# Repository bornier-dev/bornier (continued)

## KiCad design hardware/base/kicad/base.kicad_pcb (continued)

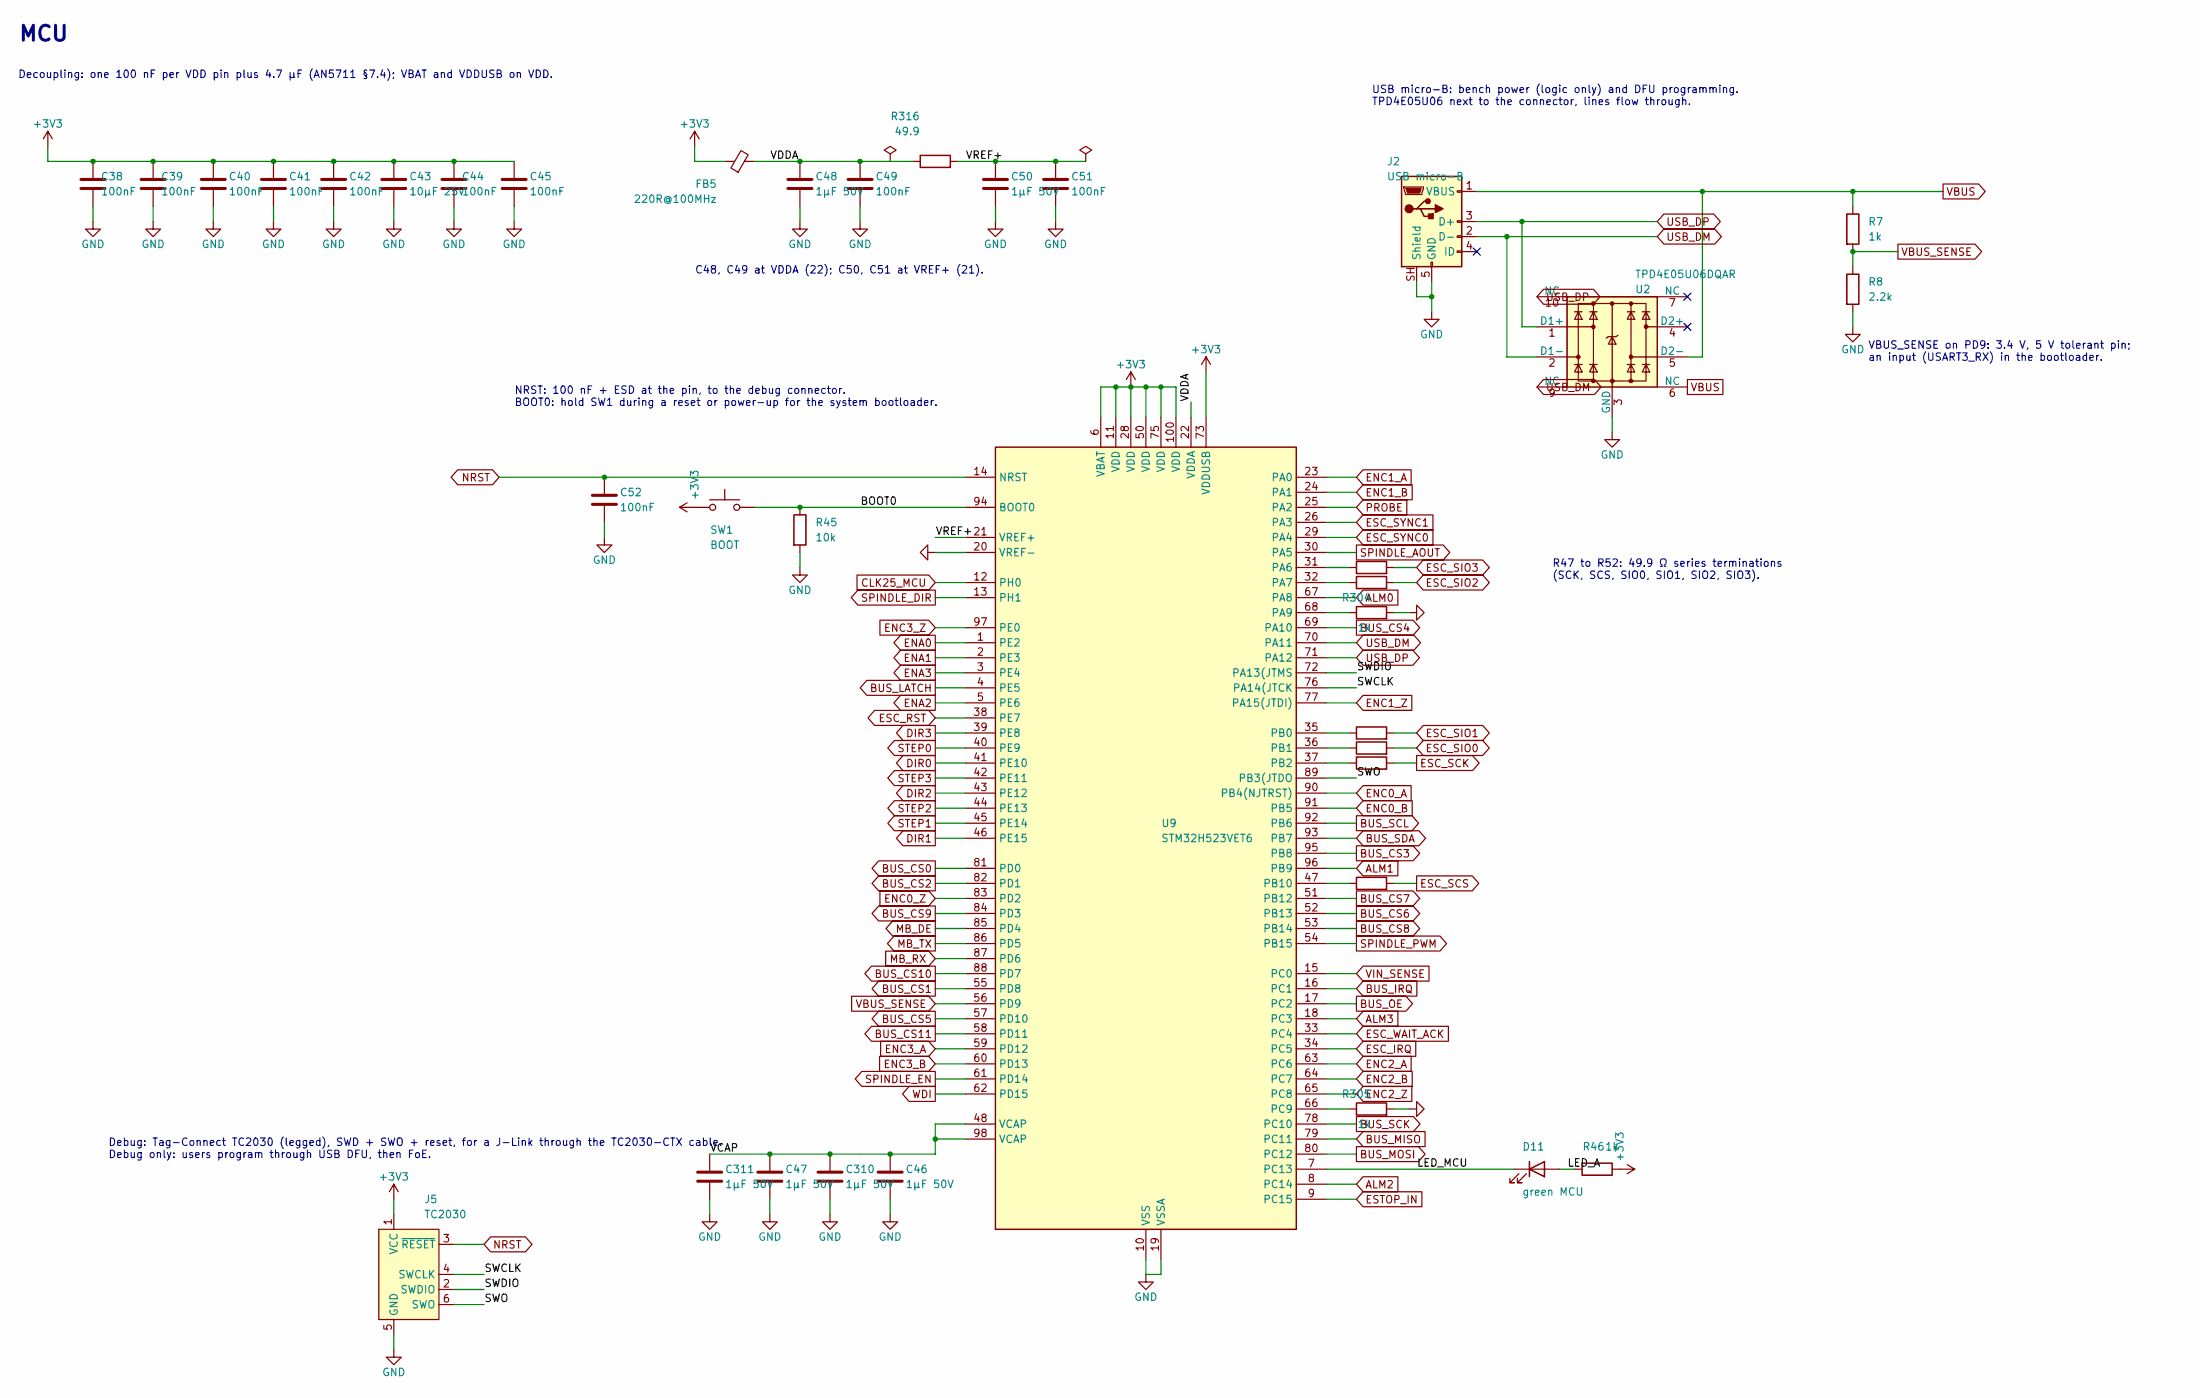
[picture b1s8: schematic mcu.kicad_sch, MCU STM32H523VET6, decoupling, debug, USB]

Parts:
C38, C39, C40, C41, C42, C44, C45, C49, C51, C52: 100nF; C_0402_1005Metric; LCSC C307331
C43: 10µF 25V; C_0805_2012Metric; LCSC C15850
C46, C47, C48, C50, C310, C311: 1µF 50V; C_0603_1608Metric; LCSC C15849
D11: green MCU; LED_0603_1608Metric; LCSC C2289
FB5: 220R@100MHz; L_0603_1608Metric; LCSC C80165
J2: USB micro-B; USB_Micro-B_Molex-105133-0001; LCSC C782257
J5: TC2030; Tag-Connect_TC2030-IDC-FP_2x03_P1.27mm_Vertical
R7, R46, R304, R305: 1k; R_0402_1005Metric; LCSC C11702
R8: 2.2k; R_0402_1005Metric; LCSC C25879
R45: 10k; R_0402_1005Metric; LCSC C25744
R47, R48, R49, R50, R51, R52, R316: 49.9; R_0603_1608Metric; LCSC C23185
SW1: BOOT; SW_XKB_TS-1187A; LCSC C318884
U2: TPD4E05U06DQAR; USON-10_2.5x1.0mm_P0.5mm; LCSC C138714
U9: STM32H523VET6; LQFP-100_14x14mm_P0.5mm; LCSC C27338462

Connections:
+3V3: C38.1, C39.1, C40.1, C41.1, C42.1, C43.1, C44.1, C45.1, FB5.1, J5.1 (VCC), R46.1, SW1.1, U9.6 (VBAT), U9.11 (VDD), U9.28 (VDD), U9.50 (VDD), U9.73 (VDDUSB), U9.75 (VDD), U9.100 (VDD); also elsewhere on the board
/MCU/BOOT0: R45.1, SW1.2, U9.94 (BOOT0)
/MCU/LED_A: D11.2 (A), R46.2
/MCU/LED_MCU: D11.1 (K), U9.7 (PC13)
/MCU/SWCLK: J5.4 (SWCLK), U9.76 (PA14(JTCK)
/MCU/SWDIO: J5.2 (SWDIO), U9.72 (PA13(JTMS)
/MCU/SWO: J5.6 (SWO), U9.89 (PB3(JTDO)
/MCU/VCAP: C46.1, C47.1, C310.1, C311.1, U9.48 (VCAP), U9.98 (VCAP)
/MCU/VDDA: C48.1, C49.1, FB5.2, R316.1, U9.22 (VDDA)
/MCU/VREF+: C50.1, C51.1, R316.2, U9.21 (VREF+)
ALM0: U9.67 (PA8); also elsewhere on the board
ALM1: U9.96 (PB9); also elsewhere on the board
ALM2: U9.8 (PC14); also elsewhere on the board
ALM3: U9.18 (PC3); also elsewhere on the board
BUS_CS0: U9.81 (PD0); also elsewhere on the board
BUS_CS1: U9.55 (PD8); also elsewhere on the board
BUS_CS2: U9.82 (PD1); also elsewhere on the board
BUS_CS3: U9.95 (PB8); also elsewhere on the board
BUS_CS4: U9.69 (PA10); also elsewhere on the board
BUS_CS5: U9.57 (PD10); also elsewhere on the board
BUS_CS6: U9.52 (PB13); also elsewhere on the board
BUS_CS7: U9.51 (PB12); also elsewhere on the board
BUS_CS8: U9.53 (PB14); also elsewhere on the board
BUS_CS9: U9.84 (PD3); also elsewhere on the board
BUS_CS10: U9.88 (PD7); also elsewhere on the board
BUS_CS11: U9.58 (PD11); also elsewhere on the board
BUS_IRQ: U9.16 (PC1); also elsewhere on the board
BUS_LATCH: U9.4 (PE5); also elsewhere on the board
BUS_MISO: U9.79 (PC11); also elsewhere on the board
BUS_MOSI: U9.80 (PC12); also elsewhere on the board
BUS_OE: U9.17 (PC2); also elsewhere on the board
BUS_SCK: U9.78 (PC10); also elsewhere on the board
BUS_SCL: U9.92 (PB6); also elsewhere on the board
BUS_SDA: U9.93 (PB7); also elsewhere on the board
CLK25_MCU: U9.12 (PH0); also elsewhere on the board
DIR0: U9.41 (PE10); also elsewhere on the board
DIR1: U9.46 (PE15); also elsewhere on the board
DIR2: U9.43 (PE12); also elsewhere on the board
DIR3: U9.39 (PE8); also elsewhere on the board
ENA0: U9.1 (PE2); also elsewhere on the board
ENA1: U9.2 (PE3); also elsewhere on the board
ENA2: U9.5 (PE6); also elsewhere on the board
ENA3: U9.3 (PE4); also elsewhere on the board
ENC0_A: U9.90 (PB4(NJTRST)); also elsewhere on the board
ENC0_B: U9.91 (PB5); also elsewhere on the board
ENC0_Z: U9.83 (PD2); also elsewhere on the board
ENC1_A: U9.23 (PA0); also elsewhere on the board
ENC1_B: U9.24 (PA1); also elsewhere on the board
ENC1_Z: U9.77 (PA15(JTDI)); also elsewhere on the board
ENC2_A: U9.63 (PC6); also elsewhere on the board
ENC2_B: U9.64 (PC7); also elsewhere on the board
ENC2_Z: U9.65 (PC8); also elsewhere on the board
ENC3_A: U9.59 (PD12); also elsewhere on the board
ENC3_B: U9.60 (PD13); also elsewhere on the board
ENC3_Z: U9.97 (PE0); also elsewhere on the board
ESC_IRQ: U9.34 (PC5); also elsewhere on the board
ESC_RST: U9.38 (PE7); also elsewhere on the board
ESC_SCK: R47.2; also elsewhere on the board
ESC_SCS: R48.2; also elsewhere on the board
ESC_SIO0: R49.2; also elsewhere on the board
ESC_SIO1: R50.2; also elsewhere on the board
ESC_SIO2: R51.2; also elsewhere on the board
ESC_SIO3: R52.2; also elsewhere on the board
ESC_SYNC0: U9.29 (PA4); also elsewhere on the board
ESC_SYNC1: U9.26 (PA3); also elsewhere on the board
ESC_WAIT_ACK: U9.33 (PC4); also elsewhere on the board
ESTOP_IN: U9.9 (PC15); also elsewhere on the board
GND: C38.2, C39.2, C40.2, C41.2, C42.2, C43.2, C44.2, C45.2, C46.2, C47.2, C48.2, C49.2, C50.2, C51.2, C52.2, C310.2, C311.2, J2.5 (GND), J2.SH (Shield), J5.5 (GND), R8.2, R45.2, R304.2, R305.2, U2.3 (GND), U2.8 (GND), U9.10 (VSS), U9.19 (VSSA), U9.20 (VREF-), U9.27 (VSS), U9.49 (VSS), U9.74 (VSS), U9.99 (VSS); also elsewhere on the board
MB_DE: U9.85 (PD4); also elsewhere on the board
MB_RX: U9.87 (PD6); also elsewhere on the board
MB_TX: U9.86 (PD5); also elsewhere on the board
NRST: C52.1, J5.3 (~RESET), U9.14 (NRST); also elsewhere on the board
unnamed: R52.1, U9.31 (PA6)
unnamed: R51.1, U9.32 (PA7)
unnamed: R304.1, U9.68 (PA9)
unnamed: R50.1, U9.35 (PB0)
unnamed: R49.1, U9.36 (PB1)
unnamed: R47.1, U9.37 (PB2)
unnamed: R48.1, U9.47 (PB10)
unnamed: R305.1, U9.66 (PC9)
PROBE: U9.25 (PA2); also elsewhere on the board
SPINDLE_AOUT: U9.30 (PA5); also elsewhere on the board
SPINDLE_DIR: U9.13 (PH1); also elsewhere on the board
SPINDLE_EN: U9.61 (PD14); also elsewhere on the board
SPINDLE_PWM: U9.54 (PB15); also elsewhere on the board
STEP0: U9.40 (PE9); also elsewhere on the board
STEP1: U9.45 (PE14); also elsewhere on the board
STEP2: U9.44 (PE13); also elsewhere on the board
STEP3: U9.42 (PE11); also elsewhere on the board
USB_DM: J2.2 (D-), U2.2 (D1-), U2.9 (NC), U9.70 (PA11)
USB_DP: J2.3 (D+), U2.1 (D1+), U2.10 (NC), U9.71 (PA12)
VBUS: J2.1 (VBUS), R7.1, U2.5 (D2-), U2.6 (NC); also elsewhere on the board
VBUS_SENSE: R7.2, R8.1, U9.56 (PD9)
VIN_SENSE: U9.15 (PC0); also elsewhere on the board
WDI: U9.62 (PD15); also elsewhere on the board

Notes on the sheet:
MCU
Decoupling: one 100 nF per VDD pin plus 4.7 µF (AN5711 §7.4); VBAT and VDDUSB on VDD.
C48, C49 at VDDA (22); C50, C51 at VREF+ (21).
NRST: 100 nF + ESD at the pin, to the debug connector. BOOT0: hold SW1 during a reset or power-up for the system bootloader.
R47 to R52: 49.9 Ω series terminations (SCK, SCS, SIO0, SIO1, SIO2, SIO3).
Debug: Tag-Connect TC2030 (legged), SWD + SWO + reset, for a J-Link through the TC2030-CTX cable. Debug only: users program through USB DFU, then FoE.
USB micro-B: bench power (logic only) and DFU programming. TPD4E05U06 next to the connector, lines flow through.
VBUS_SENSE on PD9: 3.4 V, 5 V tolerant pin; an input (USART3_RX) in the bootloader.

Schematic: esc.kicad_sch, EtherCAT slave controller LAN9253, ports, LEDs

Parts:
C13, C14, C15, C16, C17, C18, C22, C23, C24, C26, C28, C30, C31, C33, C35, C36: 100nF; C_0402_1005Metric; LCSC C307331
C19: 10µF 25V; C_0805_2012Metric; LCSC C15850
C20, C25, C27, C29, C32: 1µF 50V; C_0603_1608Metric; LCSC C15849
C21: 470pF; C_0402_1005Metric; LCSC C1537
C34: 100nF; C_0402_1005Metric; LCSC C307331; not fitted
C37: 1nF 2kV; C_1206_3216Metric; LCSC C9196
D8: green RUN; LED_0603_1608Metric; LCSC C2289
D9: red ERR; LED_0603_1608Metric; LCSC C2286
FB1, FB2, FB3, FB4: 220R@100MHz; L_0603_1608Metric; LCSC C80165
J3: HY911105AE IN; RJ45_Hanrun_HR911105A_Horizontal; LCSC C69427
J4: HY911105AE OUT; RJ45_Hanrun_HR911105A_Horizontal; LCSC C69427
R17: 12.1k; R_0402_1005Metric; LCSC C25852
R18, R25, R26, R29, R30, R31, R32, R33, R34, R35, R36: 1k; R_0402_1005Metric; LCSC C11702
R19: 100k; R_0402_1005Metric; LCSC C25741
R20, R21, R22, R23, R24: 10k; R_0402_1005Metric; LCSC C25744
R27, R28: 4.7k; R_0402_1005Metric; LCSC C25900; not fitted
R37, R38, R39, R40, R41, R42, R43, R44: 49.9; R_0603_1608Metric; LCSC C23185
TP1: ESC_IRQ; TestPoint_Pad_D1.5mm
TP2: SYNC0; TestPoint_Pad_D1.5mm
TP3: GND; TestPoint_Pad_D1.5mm
U4: LAN9253-I/R4X; QFN-64-1EP_9x9mm_P0.5mm_EP6x6mm_ThermalVias; LCSC C5745149
U5: TPS3808G33DBVR; SOT-23-6; LCSC C43698
U6: M24C16-RMN6TP; SOIC-8_3.9x4.9mm_P1.27mm; LCSC C79946; not fitted
U7, U8: TPD4E05U06DQAR; USON-10_2.5x1.0mm_P0.5mm; LCSC C138714

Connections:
+3V3: C13.1, C14.1, C15.1, C16.1, C17.1, C18.1, C19.1, C33.1, C34.1, FB1.1, FB2.1, FB3.1, R19.2, R20.2, R21.2, R27.2, R28.2, U4.5 (VDD33), U4.7 (REG_EN), U4.14 (VDDIO), U4.20 (VDDIO), U4.32 (VDDIO), U4.37 (VDDIO), U4.47 (VDDIO), U5.5 (SENSE), U5.6 (VDD), U6.8 (VCC); also elsewhere on the board
/ESC/CLK25_OFF: R18.1, U4.8 (CLK_25/XTAL_MODE)
/ESC/EESCL: R26.1, R28.1, U4.43 (EESCL/EE_EMUL2), U6.6 (SCL)
/ESC/EESDA: R25.1, R27.1, U4.42 (EESDA/EE_EMUL1), U6.5 (SDA)
/ESC/ERR: R31.1, R32.1, U4.9 (ERRLED/100FD_B)
/ESC/ERR_A: D9.2 (A), R32.2
/ESC/LINK0: R33.1, R34.1, U4.48 (LINKACTLED0/CHIP_MODE0)
/ESC/LINK0_A: J3.9, R34.2
/ESC/LINK1: R35.1, R36.1, U4.46 (LINKACTLED1/CHIP_MODE1)
/ESC/LINK1_A: J4.9, R36.2
/ESC/RBIAS: R17.1, U4.57 (RBIAS)
/ESC/RUN: R29.1, R30.1, U4.45 (RUNLED/EE_EMUL0)
/ESC/RUN_A: D8.2 (A), R30.2
/ESC/RXA_N: J3.3 (RD+), R39.1, U4.54 (RXNA), U7.2 (D1-), U7.9 (NC)
/ESC/RXA_P: J3.6 (RD-), R40.1, U4.55 (RXPA), U7.1 (D1+), U7.10 (NC)
/ESC/RXB_N: J4.2 (TD-), R42.1, U4.61 (RXNB), U8.2 (D1-), U8.9 (NC)
/ESC/RXB_P: J4.1 (TD+), R41.1, U4.60 (RXPB), U8.1 (D1+), U8.10 (NC)
/ESC/SUP_CT: R19.1, U5.4 (CT)
/ESC/TXA_N: J3.1 (TD+), R37.1, U4.52 (TXNA), U7.4 (D2+), U7.7 (NC)
/ESC/TXA_P: J3.2 (TD-), R38.1, U4.53 (TXPA), U7.5 (D2-), U7.6 (NC)
/ESC/TXB_N: J4.6 (RD-), R44.1, U4.63 (TXNB), U8.5 (D2-), U8.6 (NC)
/ESC/TXB_P: J4.3 (RD+), R43.1, U4.62 (TXPB), U8.4 (D2+), U8.7 (NC)
/ESC/VDD12TX: C30.1, C31.1, C32.1, FB4.2, U4.56 (VDD12TX1), U4.59 (VDD12TX2)
/ESC/VDD33BIAS: C24.1, C25.1, FB1.2, U4.58 (VDD33BIAS)
/ESC/VDD33TXRX1: C26.1, C27.1, C35.1, FB2.2, J3.4 (TCT), J3.5 (RCT), R37.2, R38.2, R39.2, R40.2, U4.51 (VDD33TXRX1)
/ESC/VDD33TXRX2: C28.1, C29.1, C36.1, FB3.2, J4.4 (TCT), J4.5 (RCT), R41.2, R42.2, R43.2, R44.2, U4.64 (VDD33TXRX2)
/ESC/VDDCR: C20.1, C21.1, C22.1, C23.1, FB4.1, U4.6 (VDDCR), U4.24 (VDDCR), U4.38 (VDDCR)
CHASSIS: C37.1, J3.8, J3.SH, J4.8, J4.SH; also elsewhere on the board
CLK25_ESC: U4.1 (OSCI); also elsewhere on the board
ESC_IRQ: R21.1, TP1.1, U4.44 (IRQ); also elsewhere on the board
ESC_RST: R20.1, U4.11 (~RST), U5.1 (~RESET); also elsewhere on the board
ESC_SCK: U4.19 (SCK); also elsewhere on the board
ESC_SCS: U4.50 (~SCS); also elsewhere on the board
ESC_SIO0: U4.17 (SI/SIO0); also elsewhere on the board
ESC_SIO1: U4.13 (SO/SIO1); also elsewhere on the board
ESC_SIO2: U4.12 (SIO2); also elsewhere on the board
ESC_SIO3: U4.35 (SIO3); also elsewhere on the board
ESC_SYNC0: R22.1, TP2.1, U4.34 (SYNC0/LATCH0); also elsewhere on the board
ESC_SYNC1: R23.1, U4.18 (SYNC1/LATCH1); also elsewhere on the board
ESC_WAIT_ACK: R24.1, U4.10 (WAIT_ACK); also elsewhere on the board
GND: C13.2, C14.2, C15.2, C16.2, C17.2, C18.2, C19.2, C20.2, C21.2, C22.2, C23.2, C24.2, C25.2, C26.2, C27.2, C28.2, C29.2, C30.2, C31.2, C32.2, C33.2, C34.2, C35.2, C36.2, C37.2, D8.1 (K), D9.1 (K), J3.10, J4.10, R17.2, R18.2, R22.2, R23.2, R24.2, R25.2, R26.2, R29.2, R31.2, R33.2, R35.2, TP3.1, U4.4 (OSCVSS), U4.41 (TESTMODE), U4.65 (VSS), U5.2 (GND), U6.4 (GND), U6.7 (WP), U7.3 (GND), U7.8 (GND), U8.3 (GND), U8.8 (GND); also elsewhere on the board

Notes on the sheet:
ETHERCAT SLAVE CONTROLLER
Decoupling: one 100 nF per supply pin, at the pin (checklist p.3, p.7).
C20: 1 µF ESR 0.1 Ω + C21 470 pF at VDDCR pin 6. Ferrites: BLM18PG221SN1D, bulk on both sides.
Supervisor on RST# only: 3.07 V, 300 ms. The MCU drives RST# open drain and reads it back.
PDI: SPI, then SQI (OCTOSPI of the MCU). SYNC0/1 and WAIT_ACK pulled down: Hi-Z until the ESC is configured.
SII EEPROM emulated by the MCU (EE_EMUL = 000, PDI SPI): R25, R26 fitted. Fallback EEPROM: fit U6, C34, R27, R28 and remove R25, R26.
CLK_25 strapped low: output off. RBIAS: 12.1 kΩ 1 %.
IN: port 0 (PHY A)
OUT: port 1 (PHY B)
LED pins are straps: pulled down (2 ports, emulation, port B auto-negotiation). LINK/ACT on the green LED of each RJ45; yellow LEDs unused.

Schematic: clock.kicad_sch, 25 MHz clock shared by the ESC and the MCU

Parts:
C12: 100nF; C_0402_1005Metric; LCSC C307331
R15, R16: 49.9; R_0603_1608Metric; LCSC C23185
X1: SiT8008BI-71-33E-25.000000; Oscillator_SMD_SiT_PQFN-4Pin_2.0x1.6mm; LCSC C806295

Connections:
+3V3: C12.1, X1.1 (OE), X1.4 (Vdd); also elsewhere on the board
/Clock/CLK25: R15.1, R16.1, X1.3 (OUT)
CLK25_ESC: R15.2; also elsewhere on the board
CLK25_MCU: R16.2; also elsewhere on the board
GND: C12.2, X1.2 (GND); also elsewhere on the board

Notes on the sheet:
CLOCK
One oscillator for both chips: ESC OSCI and MCU PH0 (HSE bypass). OE tied high (datasheet: pull-up of 10 kΩ or less when not driven). R15, R16: series termination at the source.

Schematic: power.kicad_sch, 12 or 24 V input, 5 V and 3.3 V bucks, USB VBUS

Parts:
C1: 47µF 63V; CP_Elec_6.3x7.7; LCSC C46550423
C2, C3: 2.2µF 100V; C_1210_3225Metric; LCSC C153036
C4, C7, C11, C312: 100nF; C_0402_1005Metric; LCSC C307331
C5: 100µF 10V; C_1210_3225Metric; LCSC C84455
C9, C10, C300: 10µF 25V; C_0805_2012Metric; LCSC C15850
D1: SMBJ33CA; D_SMB; LCSC C78420
D2, D3, D4, D5: SS56B; D_SMB; LCSC C14651
D6, D7, D300: green; LED_0603_1608Metric; LCSC C2289
F1: 3.5A 63V; Fuse_1206_3216Metric; LCSC C182975
J1: POWER; PhoenixContact_MC_1,5_4-G-3.81_1x04_P3.81mm_Horizontal; LCSC C441184
L1: 8.2µH; L_Sunlord_MWSA1004S; LCSC C408486
L2: 1µH; L_1008_2520Metric; LCSC C435392
Q11: AO3401A; SOT-23; LCSC C15127
R1, R3, R11, R300, R308, R311: 100k; R_0402_1005Metric; LCSC C25741
R2, R4, R301: 47k; R_0402_1005Metric; LCSC C25792
R5, R9: 10k; R_0402_1005Metric; LCSC C25744
R6, R302: 12.1k; R_0402_1005Metric; LCSC C25852
R10: 2.2k; R_0402_1005Metric; LCSC C25879
R12: 4.7k; R_0402_1005Metric; LCSC C25900
R13, R306: 4.7k; R_1206_3216Metric; LCSC C17936
R14, R303, R310: 1k; R_0402_1005Metric; LCSC C11702
TP4: +VIN; TestPoint_Pad_D1.5mm
TP5: +VIN_OUT; TestPoint_Pad_D1.5mm
TP6: +5V; TestPoint_Pad_D1.5mm
TP7: +3V3; TestPoint_Pad_D1.5mm
U1: TPS54360BDDAR; TI_SO-PowerPAD-8_ThermalVias; LCSC C524806
U3: TPS62A02ADRLR; SOT-563; LCSC C5820994

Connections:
+3V3: C10.1, C300.1, L2.2, R9.1, R14.1, TP7.1; also elsewhere on the board
+5V: C5.1, D4.2 (A), L1.2, R4.1, R310.1, TP6.1; also elsewhere on the board
+VIN: C1.1, C2.1, C3.1, D2.1 (K), R1.1, R11.1, R13.1, TP4.1, U1.2 (VIN); also elsewhere on the board
+VIN_OUT: R306.1, TP5.1; also elsewhere on the board
/Power/BOOT: C4.1, U1.1 (BOOT)
/Power/COMP: R6.1, U1.6 (COMP)
/Power/COMPZ: C7.1, R6.2
/Power/EN: R2.1, R300.2, R308.1, U1.3 (EN)
/Power/FB3: R9.2, R10.1, U3.5 (FB)
/Power/FB5: R5.1, R302.2, U1.5 (FB)
/Power/LED3V3: D7.2 (A), R14.2
/Power/LEDVIN: D6.2 (A), R13.2
/Power/LEDVOUT: D300.2 (A), R306.2
/Power/RT: R3.1, U1.4 (RT/CLK)
/Power/SW3: L2.1, U3.2 (SW)
/Power/SW5: C4.2, D3.1 (K), L1.1, U1.8 (SW)
/Power/V3IN: C9.1, D4.1 (K), Q11.3 (D), U3.3 (VIN), U3.4 (EN)
/Power/VIN_F: D1.1 (A1), D2.2 (A), F1.2
/Power/VIN_RAW: F1.1, J1.1
CHASSIS: J1.3; also elsewhere on the board
GND: C1.2, C2.2, C3.2, C5.2, C9.2, C10.2, C11.2, C300.2, C312.2, D1.2 (A2), D3.2 (A), D6.1 (K), D7.1 (K), D300.1 (K), J1.2, R2.2, R10.2, R12.2, R301.2, R303.2, R308.2, R311.2, U1.7 (GND), U1.9 (GNDPAD), U3.1 (GND); also elsewhere on the board
unnamed: C7.2, C312.1
unnamed: D5.1 (K), Q11.2 (S)
unnamed: Q11.1 (G), R310.2, R311.1
unnamed: R1.2, R300.1
unnamed: R3.2, R301.1
unnamed: R4.2, R302.1
unnamed: R5.2, R303.1
VBUS: D5.2 (A); also elsewhere on the board
VIN_SENSE: C11.1, R11.2, R12.1; also elsewhere on the board

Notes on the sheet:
POWER
Logic supply VIN: 12 V or 24 V, 10.8 to 30 V (24 V: IEC 61131-2, 19.2 to 30 V). Fuse, bidirectional TVS, reverse polarity diode. Condition of use: dedicated supply in the same cabinet, short wiring (no 0.5 kV / 2 ohm surge immunity, see ../sim/README.md).
VOUT = 0.8 V x (1 + (R4 + R302)/(R5 + R303)) = 5.10 V, above VBUS; fsw = 658 kHz (R3 + R301 = 147 k). Compensation R6, C7 taken from the passive palette, simulated (sim/README.md). UVLO (R1 + R300 = 200 k, R2 // R308 = 32.0 k): start 8.47 V (9.48 V worst case), stop 7.79 V. 60 V parts throughout: t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
VBUS from the USB jack (MCU sheet): bench power, logic only.
VOUT = 0.6 V x (1 + R9/R10) = 3.33 V TPS62A02A: 2 A, forced PWM at 2.4 MHz. L2 1 µH, C10 + C300 = 2 x 10 µF (TI: 1 µH, 22 µF). PG (pin 6) left open. D4, D5: 5 V rail and USB VBUS OR-ed, no backfeed.
Supply monitoring and power LEDs
R11/R12: 73.5 V full scale on the 3.3 V ADC.
Test points of the rails.

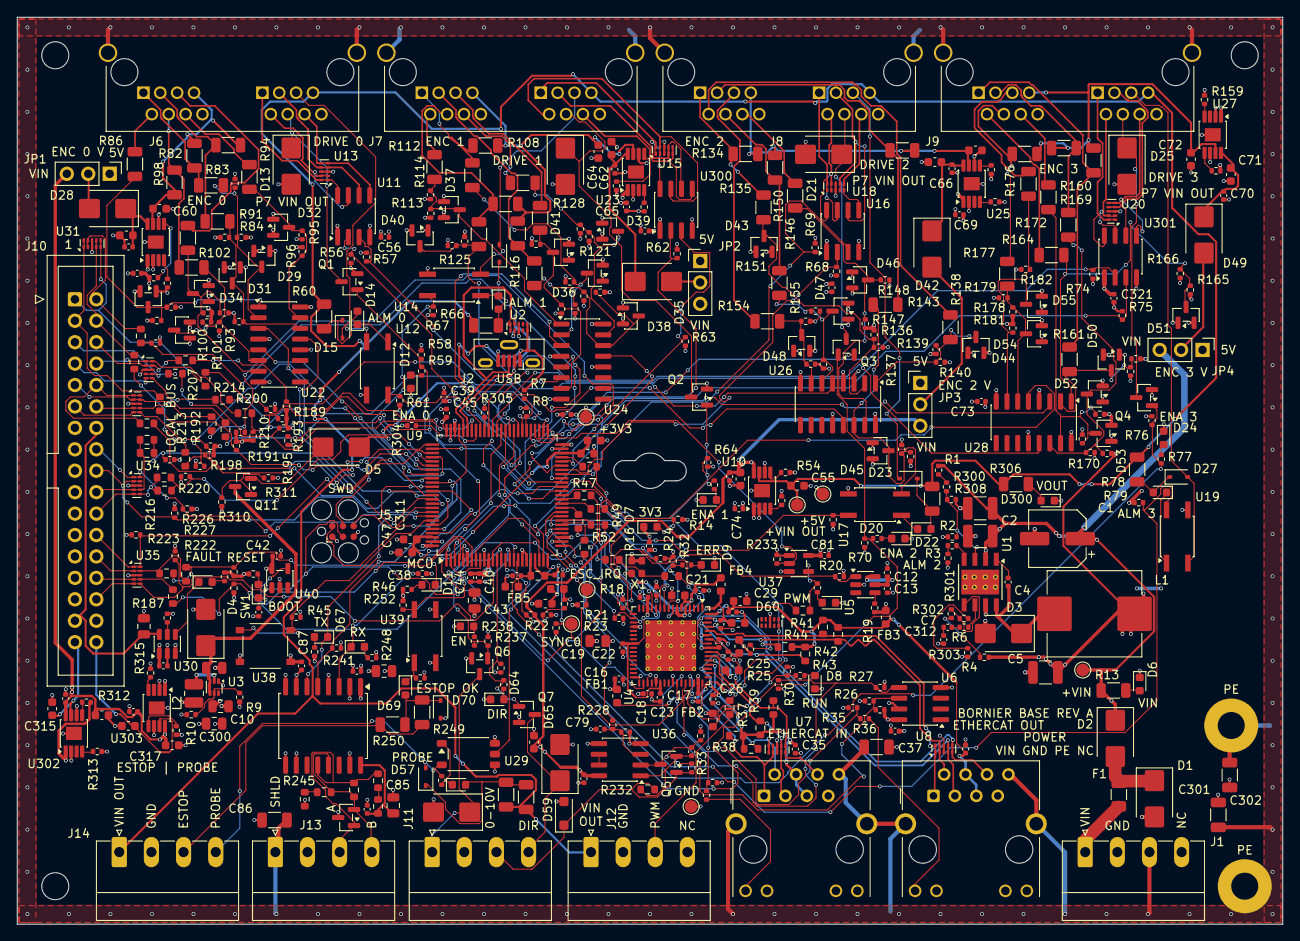
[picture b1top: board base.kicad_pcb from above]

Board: 4 copper layers, 150.0 x 107.5 mm, 517 parts (0 on the bottom side), 309 nets.

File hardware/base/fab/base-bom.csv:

Comment,Designator,Footprint,LCSC Part #
TLP2361,U29,SO-5-6_4.55x3.7mm_P1.27mm,C107626
1k,"R14,R18,R188,R228,R238,R240,R247,R248,R25,R251,R253,R26,R29,R30,R303,R304,R305,R31,R310,R313,R315,R32,R33,R34,R35,R36,R46,R55,R59,R65,R7,R71,R77",R_0402_1005Metric,C11702
LTV-357T-C,"U12,U14,U17,U19,U39",SO-4_4.4x3.6mm_P2.54mm,C119091
SMF15A,D59,D_SOD-123F,C123802
BAT54S,"D29,D30,D31,D32,D33,D34,D36,D37,D38,D39,D40,D41,D43,D44,D45,D46,D47,D48,D50,D51,D52,D53,D54,D55",SOT-23,C12765
TPD4E05U06DQAR,"D60,U13,U15,U18,U2,U20,U31,U32,U33,U34,U35,U7,U8",USON-10_2.5x1.0mm_P0.5mm,C138714
SS56B,"D2,D28,D3,D35,D4,D42,D49,D5",D_SMB,C14651
AO3401A,Q11,SOT-23,C15127
2.2uF 100V,"C2,C3",C_1210_3225Metric,C153036
470pF,"C21,C80",C_0402_1005Metric,C1537
1uF 50V,"C20,C25,C27,C29,C310,C311,C314,C315,C317,C318,C32,C46,C47,C48,C50,C54,C55,C59,C60,C63,C64,C67,C68,C71,C72,C78",C_0603_1608Metric,C15849
10uF 25V,"C10,C19,C300,C43,C76,C83,C85,C9",C_0805_2012Metric,C15850
4.7k,"R108,R116,R124,R13,R134,R142,R150,R160,R168,R176,R184,R185,R249,R250,R306,R60,R66,R72,R78,R82,R90,R98",R_1206_3216Metric,C17936
3.5A 63V,F1,Fuse_1206_3216Metric,C182975
TPS3828-33DBVR,U40,SOT-23-5,C20032
OPA2990IDR,U36,SOIC-8_3.9x4.9mm_P1.27mm,C2058283
LOCAL BUS,J10,IDC-Header_2x17_P2.54mm_Vertical,C20920
1N4148WS,"D15,D19,D23,D27,D57,D70",D_SOD-323,C2128
120,"R232,R234,R235,R242,R243,R244,R245,R246",R_0603_1608Metric,C22787
red ALM,"D14,D18,D22,D26,D58,D71,D9",LED_0603_1608Metric,C2286
green MCU,"D11,D12,D16,D20,D24,D300,D56,D6,D61,D62,D64,D67,D68,D69,D7,D8",LED_0603_1608Metric,C2289
49.9,"R15,R16,R203,R204,R205,R206,R207,R208,R209,R210,R211,R212,R213,R214,R215,R216,R217,R218,R219,R220,R221,R316,R37,R38,R39,R40,R41,R42,R43,R44,R47,R48,R49,R50,R51,R52",R_0603_1608Metric,C23185
100k,"R1,R11,R19,R223,R224,R225,R229,R233,R237,R239,R3,R300,R308,R311,R58,R64,R70,R76",R_0402_1005Metric,C25741
10k,"R106,R132,R158,R189,R190,R191,R192,R193,R194,R195,R196,R197,R198,R199,R20,R200,R201,R202,R21,R22,R222,R23,R230,R24,R241,R252,R312,R314,R45,R5,R54,R56,R57,R61,R62,R63,R67,R68,R69,R73,R74,R75,R79,R80,R9",R_0402_1005Metric,C25744
47k,"R187,R2,R301,R4",R_0402_1005Metric,C25792
12.1k,"R17,R302,R6",R_0402_1005Metric,C25852
2.2k,"R10,R107,R133,R159,R226,R227,R236,R8,R81",R_0402_1005Metric,C25879
4.7k,"R100,R101,R103,R104,R110,R111,R113,R114,R118,R119,R12,R121,R122,R126,R127,R129,R130,R136,R137,R139,R140,R144,R145,R147,R148,R152,R153,R155,R156,R162,R163,R165,R166,R170,R171,R173,R174,R178,R179,R181,R182,R186,R231,R84,R85,R87,R88,R92,R93,R95,R96",R_0402_1005Metric,C25900
3.3k,"R102,R109,R112,R117,R120,R125,R128,R135,R138,R143,R146,R151,R154,R161,R164,R169,R172,R177,R180,R83,R86,R91,R94,R99",R_1206_3216Metric,C26032
TPS1H000AQDGNRQ1,"U10,U21,U23,U25,U27,U302,U303",HVSSOP-8-1EP_3x3mm_P0.65mm_EP1.57x1.89mm,C2653764
STM32H523VET6,U9,LQFP-100_14x14mm_P0.5mm,C27338462
SN75ALS191DR,"U11,U16,U300,U301",SOIC-8_3.9x4.9mm_P1.27mm,C2871261
CA-IS3092W,U38,SOIC-16W_7.5x10.3mm_P1.27mm,C2890051
ENC 5V|VIN,"JP1,JP2,JP3,JP4",PinHeader_1x03_P2.54mm_Vertical,C2937625
100nF,"C11,C12,C13,C14,C15,C16,C17,C18,C22,C23,C24,C26,C28,C30,C31,C312,C313,C316,C320,C321,C33,C35,C36,C38,C39,C4,C40,C41,C42,C44,C45,C49,C51,C52,C53,C56,C57,C58,C61,C62,C65,C66,C69,C7,C70,C73,C74,C75,C77,C79,C81,C82,C84,C87",C_0402_1005Metric,C307331
BOOT,SW1,SW_XKB_TS-1187A,C318884
PSM712-LF-T7,D66,SOT-23,C32677
AO3422,"Q1,Q2,Q3,Q4,Q6,Q7",SOT-23,C37130
8.2uH,L1,L_Sunlord_MWSA1004S,C408486
1uH,L2,L_1008_2520Metric,C435392
TPS3808G33DBVR,U5,SOT-23-6,C43698
POWER,"J1,J11,J12,J13,J14","PhoenixContact_MC_1,5_4-G-3.81_1x04_P3.81mm_Horizontal",C441184
47uF 63V,C1,CP_Elec_6.3x7.7,C46550423
TPS54360BDDAR,U1,TI_SO-PowerPAD-8_ThermalVias,C524806
AM26LV32EIDR,"U22,U24,U26,U28",SOIC-16_3.9x9.9mm_P1.27mm,C527448
TPS2553DBVR,U30,SOT-23-6,C55266
LAN9253-I/R4X,U4,QFN-64-1EP_9x9mm_P0.5mm_EP6x6mm_ThermalVias,C5745149
TPS62A02ADRLR,U3,SOT-563,C5820994
HY911105AE IN,"J3,J4",RJ45_Hanrun_HR911105A_Horizontal,C69427
SN74AHCT1G125DBVR,U37,SOT-23-5,C7484
HC-WK88-H132-1X2-55B,"J6,J7,J8,J9",RJ45x2_HongCheng_HC-WK88-H132-1X2-55B,C7501828
USB micro-B,J2,USB_Micro-B_Molex-105133-0001,C782257
SMBJ33CA,"D1,D13,D17,D21,D25,D63,D65",D_SMB,C78420
220R@100MHz,"FB1,FB2,FB3,FB4,FB5",L_0603_1608Metric,C80165
SiT8008BI-71-33E-25.000000,X1,Oscillator_SMD_SiT_PQFN-4Pin_2.0x1.6mm,C806295
100uF 10V,C5,C_1210_3225Metric,C84455
SS8550,Q5,SOT-23,C8542
1nF 2kV,"C301,C302,C37,C86",C_1206_3216Metric,C9196

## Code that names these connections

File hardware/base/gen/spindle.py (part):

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    cx, cy = 132.08, 83.82
    s.place(u, cx, cy, ref_at=(cx - 5.08, cy - 15.24), val_at=(cx - 5.08, cy - 17.78))
    P = lambda n: s.P(u, n)  # noqa: E731
    rin = next(r for r in on("SP_DAC", "R") if "SPINDLE_AOUT" in c.by_ref()[r]["pins"].values())
    rpd = next(r for r in on("SP_DAC", "R") if r != rin)
    cin = on("SP_DAC", "C")[0]
    ax, ay = P(3)
    hr(s, rin, ax - 27.94, ay, rot=90 if c.by_ref()[rin]["pins"]["1"] == "SPINDLE_AOUT" else 270)
    a, b = sorted((s.P(rin, 1), s.P(rin, 2)))
    s.w("SPINDLE_AOUT", a, (a[0] - 10.16, ay))
    s.glabel("SPINDLE_AOUT", a[0] - 10.16, ay, 180, "input")
    s.w("SP_DAC", b, (ax, ay))
    vr(s, cin, ax - 17.78, ay)
    s.rail("GND", *s.P(cin, 2))
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    rg = next(r for r in on("SP_FB", "R") if c.by_ref()[r]["value"] == "4.7k")
    yf = cy + 17.78
    s.w("SP_FB", (nx, ny), (nx - 2.54, ny), (nx - 2.54, yf))
    hr(s, rf, cx, yf, rot=270 if c.by_ref()[rf]["pins"]["1"] == "SP_AOUT" else 90,
       ref_at=(cx - 3.81, yf - 2.54), val_at=(cx - 2.54, yf + 3.81))
    fa, fb = sorted((s.P(rf, 1), s.P(rf, 2)))
    s.w("SP_FB", (nx - 2.54, yf), fa)
    s.label("SP_FB", nx, yf)
    vr(s, rg, nx - 2.54, yf, dx=-5.08)
    s.rail("GND", *s.P(rg, 2))
    gx4, gy4 = P(4)
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    vr(s, cf, ox + 3.81, oy)
    cfb = s.P(cf, 2)
    s.w("SP_FB", cfb, (cfb[0] + 2.54, cfb[1]))
    s.label("SP_FB", cfb[0] + 2.54, cfb[1])
    s.w("SP_AOUT", ro, (ro[0] + 15.24, oy))
    s.label("SP_AOUT", ro[0] + 15.24, oy)
    s.place(tvs, ro[0] + 7.62, oy + 3.81, rot=270, ref_at=(ro[0] + 10.16, oy + 3.81), val_at=(ro[0] + 10.16, oy + 6.35))
    s.rail("GND", *(sorted((s.P(tvs, 1), s.P(tvs, 2)), key=lambda p: p[1])[1]))
    # current limit: PNP across the 120 ohm, collector into SP_FB
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    s.w("SP_OA", (ex_, ey_), (lo[0], ey_), lo)
    kx_, ky_ = s.P(q, 3)
    s.w("SP_FB", (kx_, ky_), (kx_ + 5.08, ky_))
    s.label("SP_FB", kx_ + 5.08, ky_)
    # supply of the op amp: +VIN, decoupled at the pin, routed over the follower of the unused half
    vx, vy = P(8)
    xv, yr = vx + 5.08, cy - 33.02
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    s.place(ub, bx_, by_, ref_at=(bx_ + 5.08, by_ - 12.7), val_at=(bx_ + 5.08, by_ - 15.24))
    Pb = lambda n: s.P(ub, n)  # noqa: E731
    ix, iy = Pb(2)
    rpd = next(r for r in on("SPINDLE_PWM", "R"))
    s.w("SPINDLE_PWM", (ix, iy), (ix - 25.4, iy))
    s.glabel("SPINDLE_PWM", ix - 25.4, iy, 180, "input")
    vr(s, rpd, ix - 10.16, iy, dx=-5.08)
    s.rail("GND", *s.P(rpd, 2))
    ex, ey = Pb(1)
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    rs2 = next(r for r in on("SP_PWM_C", "R") if r != rs)
    hr(s, rs, yx + 13.97, yy, rot=90 if c.by_ref()[rs]["pins"]["1"] == "SP_PWM_B" else 270)
    s.w("SP_PWM_B", (yx, yy), sorted((s.P(rs, 1), s.P(rs, 2)))[0])
    hr(s, rs2, yx + 21.59, yy, rot=90 if c.by_ref()[rs2]["pins"]["1"] == "SP_PWM_C" else 270)
    s.quiet.add("SP_PWM_C")
    # ESD between the two 120 ohm
    tp = next(d for d in on("SP_PWM_C", "D"))
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    s.place(tp, jx_ + 2.54, yy + 20.32, rot=270, mirror="y", ref_at=(jx_ - 2.54, yy + 35.56),
            val_at=(jx_ - 2.54, yy + 38.1))
    s.w("SP_PWM_C", (jx_, yy), s.P(tp, 1))
    s.label("SP_PWM_C", *s.P(tp, 1), tag=f"{tp}.1")
    s.label("SP_PWM_C", *s.P(tp, 10), tag=f"{tp}.10")     # flow-through: the NC pin opposite carries the line
    s.rail("GND", *s.P(tp, 3))
    re = sorted((s.P(rs2, 1), s.P(rs2, 2)))[1]
    s.w("SP_PWM", re, (re[0] + 20.32, yy))
    s.label("SP_PWM", re[0] + 20.32, yy)
    rl = next(r for r in on("SP_PWM_LA", "R"))
    dl = on("SP_PWM_LA", "D")[0]
    vr(s, rl, yx + 5.08, yy)
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    s.quiet.update({"SP_PWM_B", "SP_PWM_LA"})

    # --- EN and DIR -------------------------------------------------------------------------------
    for k, (sig, net) in enumerate((("SPINDLE_EN", "SP_EN"), ("SPINDLE_DIR", "SP_DIR"))):
        q = on(net, "Q")[0]
        qx, qy = 241.3 + 76.2 * k, 165.1
        s.place(q, qx, qy, ref_at=(qx + 5.08, qy - 1.27), val_at=(qx + 5.08, qy + 1.27))
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
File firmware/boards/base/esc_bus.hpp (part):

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 *
 *          | Signal   | Pin  | Function            |
 *          |----------|------|---------------------|
 *          | SCK      | PB2  | OCTOSPI1_CLK, AF9   |
 *          | SCS#     | PB10 | OCTOSPI1_NCS, AF9   |
 *          | SI/SIO0  | PB1  | OCTOSPI1_IO0, AF6   |
 *          | SO/SIO1  | PB0  | OCTOSPI1_IO1, AF6   |
 *          | SIO2     | PA7  | OCTOSPI1_IO2, AF10  |
 *          | SIO3     | PA6  | OCTOSPI1_IO3, AF6   |
 *
 *          Two bus modes:
 *
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		rcc.ahb2enr |= (rcc_p::ahb2enr_r::gpioaen_f() | rcc_p::ahb2enr_r::gpioben_f()) | atomic;
		rcc.ahb4enr |= rcc_p::ahb4enr_r::octospi1en_f() | atomic;

		gpioa.afrl <<= gpio_p::afrl_r::afsel6_f(6) || atomic;  // PA6  IO3
		gpioa.afrl <<= gpio_p::afrl_r::afsel7_f(10) || atomic; // PA7  IO2
		gpiob.afrl <<= gpio_p::afrl_r::afsel0_f(6) || atomic;  // PB0  IO1
		gpiob.afrl <<= gpio_p::afrl_r::afsel1_f(6) || atomic;  // PB1  IO0
		gpiob.afrl <<= gpio_p::afrl_r::afsel2_f(9) || atomic;  // PB2  CLK
		gpiob.afrh <<= gpio_p::afrh_r::afsel10_f(9) || atomic; // PB10 NCS

		// High speed (0b10) on the six pins, then alternate function mode (0b10).
		gpioa.ospeedr <<= gpio_p::ospeedr_r::ospeed6_f(0b10) || atomic;
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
